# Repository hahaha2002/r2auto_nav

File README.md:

# r2auto_nav
Tánkyu 2310i <br/>
Group 2, Studio 2 <br/>
Ang Kai Jun, David Chong Joon Wei, Ha Zhe Li, Rayner Lim Fang Yuh, Wang Yanxiao Austin <br/>

EG2310 - Fundamentals of Systems Design, AY 21/22, <br/>
Innoovation and Design Programme, National University of Singapore (NUS). <br/>

## Description
The Tánkyu 2310i, developed by NUS IDP students from EG2310, is a modified Robotis Co. Turtlebot 3. It is augmented with LIDAR, NFC-detection, IR-detection and a flywheel firing system to accomplish its set objectives - Autonomous navigation within a closed and connected maze, locating a loading bay demarcated by NFC tags, and firing a ping-pong ball at a target with high IR-signature.

In this repository, we are using Ubuntu 20.04.4, ROS2 Foxy and Python3.6 to explore a closed and connected maze using a left-wall following algorithm.
You may check out our project report under the [Documentations](https://github.com/hahaha2002/r2auto_nav/tree/main/Documentations) folder for more details on our robot and its mission.

## File Organisation
- [Documentations](https://github.com/hahaha2002/r2auto_nav/tree/main/Documentations) folder contain all the documentation of the Tánkyu 2310i, this includes the project report, assembly manual, full software setup guide and end user documentation.
- [navigation.py](https://github.com/hahaha2002/r2auto_nav/blob/main/navigation.py) code contains the main system and wall-following logic. This code also communicates with the mission code to allow the Tánkyu 2310i to engage on the ir signature when the conditions are met.
- [mission.py](https://github.com/hahaha2002/r2auto_nav/blob/main/mission.py) code initiates all the i2c connections and contain the firing algorithm. This code performs all necessary logic processing with the input from the NFC and IR detection systems and communicates the information to the navigation code to allow the Tánkyu 2310i to engage on the ir signature when the conditions are met.
- [Ubuntu_Files](https://github.com/hahaha2002/r2auto_nav/tree/main/Ubuntu_Files) folder is an archive of the miscellaneous code that was tested but not implemented into the final system. The code are functional independently but requires some edits to integrate it into the final system.
- [RPi_Files](https://github.com/hahaha2002/r2auto_nav/tree/main/RPi_Files) folder contains the [factory acceptance test codes](https://github.com/hahaha2002/r2auto_nav/tree/main/RPi_Files/fac_test), all required packages and other test codes for each individual subsystem. 
- [Original_Files](https://github.com/hahaha2002/r2auto_nav/tree/main/Original_Files) folder is an archive of the forked repository from [shihchengyen's r2auto_nav_repository](https://github.com/shihchengyen/r2auto_nav) and is not necessary for the Tankyu 2310i's operations.

## Calibration and configuration
### Navigation Code
Under 'Adjustable variables to calibrate wall follower', you may experiment with different parameters to calibrate the navigation algorithm to suit your needs.
| Variable name| Description| Recommended value  |
| ------------- |:-------------| ---:|
| d | Distance from wall| 0.35 |
| fd| Front distance when approaching a merging wall| d + 0.1|
| reverse_d | Distance to reverse when too close to front wall| 0.20|
| speedchange | Linear speed | 0.17|
| turning_speed_wf_fast| Fast rotate speed, used when avoiding obstacle in front| 0.75|
| turning_speed_wf_slow| Slow rotate speed, used when reversing, finding wall or too close to wall| 0.40|
| snaking_radius | Distance from wall before correcting drift | d - 0.07|
| cornering_speed_constant | Coefficient of speedchange during cornering to prevent over/under steer| 0.5|

### Mission Code
Under 'Adjustable variables to calibrate targeting' you may experiment with different parameters to calibrate the targeting algorithm to suit your needs.
| Variable name| Description| Recommended value  |
| ------------- |:-------------| ---:|
| rotatechange | Angular speed| 0.35 |
| speedchange | Linear speed | 0.20 |
| min_temp_threshold | IR live feed minimum value reference (Appears blue) | 30.0|
| max_temp_threshold | IR live feed maximum value reference (Appears red) | 35.0|
| detecting_threshold | Minimum temperature to identify target as a "Hot target" | 32.0|
| firing_threshold | Acts as a second check after centering target | 35.0|
| ir_offset | Offset angle for each IR sensor orientation (0°→0, 45°→31, 90°→69) | 31.0|

## Operating Instructions

### Installation
Tested on Ubuntu 20.04 - ROS2 Foxy <br/>
For beginners, follow our step-by-step software setup guide in our [documentations](https://github.com/hahaha2002/r2auto_nav/tree/main/Documentations) folder.<br/>
For M1 MacBook users, refer to our [video guide](https://youtu.be/suntoEurFio) for Ubuntu setup and installation. <br/>

1. Install Ubuntu 20.04 and ROS 2 Foxy using the instructions in Section 3.1 of the [Robotis e-manual](https://emanual.robotis.com/docs/en/platform/turtlebot3/quick-start/#pc-setup) (Ensure you click on the "Foxy" tab).
3. Using Ubuntu, complete the RPi in Section 3.2
4. Using Ubuntu, complete the OpenCR setup in Section 3.3 

### Set Up
1. Clone this repository onto your Ubuntu ros2 directory: <br/>
``` 
cd colcon_ws/src/auto_nav
git clone https://github.com/hahaha2002/r2auto_nav.git 
cd colcon_ws
colcon build
```
2. Copy mission.py and the RPi_files folder to the RPi: <br/>
``` 
scp -r <path to r2auto_nav directory>/mission.py ubuntu@<RPi IP address>:~/turtlebot_ws/src 
scp -r <path to r2auto_nav directory>/RPi_files ubuntu@<RPi IP address>:~/turtlebot_ws/src 
```
3. Build the package on RPi: <br/>
``` 
cd turtlebot3_ws 
colcon build 
```
4. Install the pigpio package on RPi and automate the daemon on boot:
```
sudo apt install pigpio
sudo systemctl enable pigpiod
```

### Running Instructions
1. Ssh into the RPi, `ssh ubuntu@<RPi IP Address>`
2. On the RPi, initiate the bring up `ros2 launch turtlebot3_bringup robot.launch.py'
3. On RPi, in the RPi_files directory, Start the targeting code `python3 mission.py`.
4. On Ubuntu, in the r2auto_nav directory, Start the navigation code `python3 navigation.py`.

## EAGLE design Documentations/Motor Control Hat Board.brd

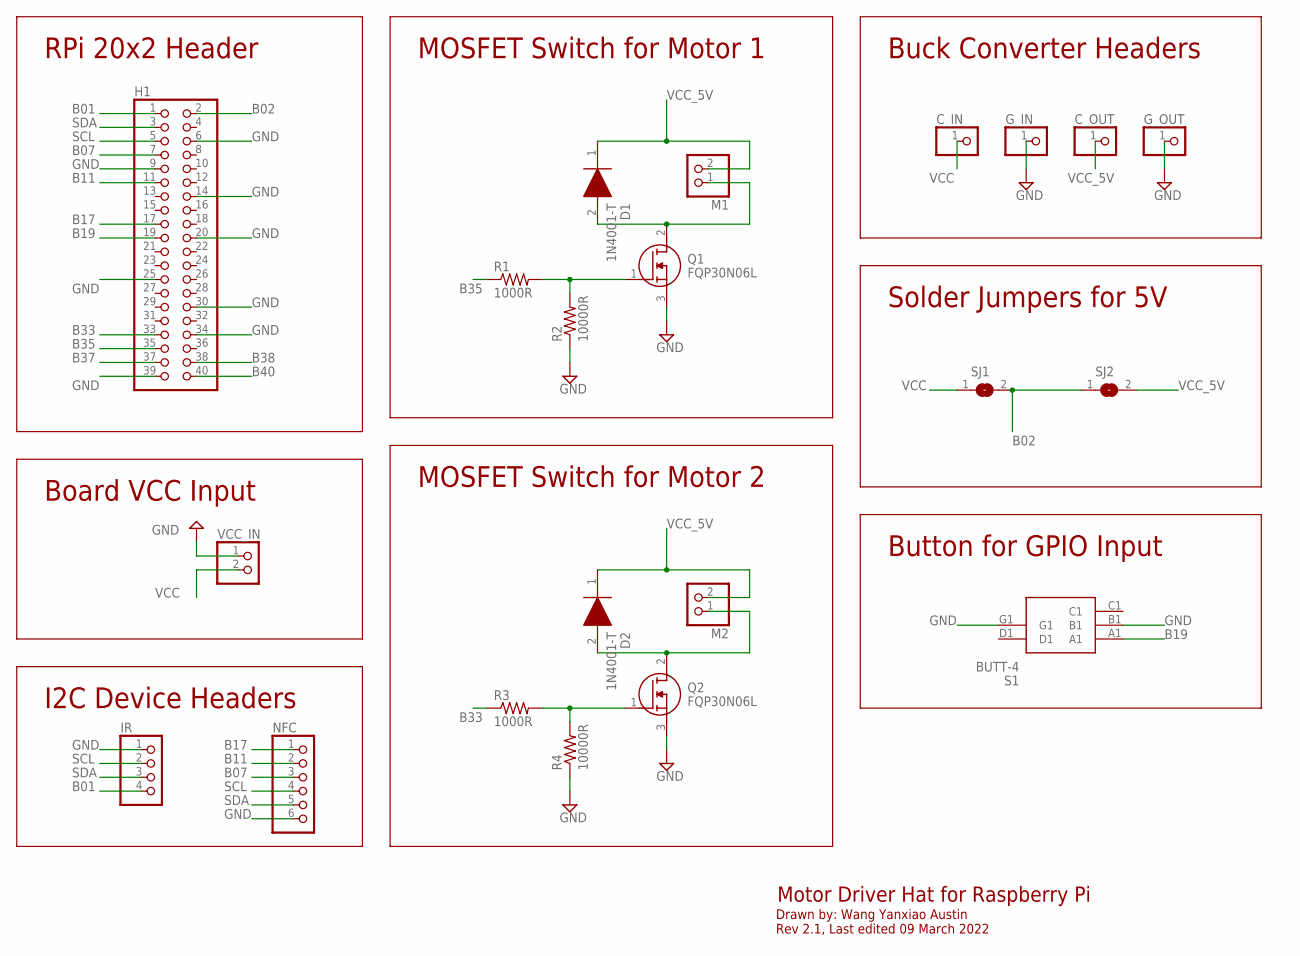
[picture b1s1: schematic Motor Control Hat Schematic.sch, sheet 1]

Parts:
C_IN: PINHD-1X1; 1X01
C_OUT: PINHD-1X1; 1X01
D1, D2: 1N4001-T; DIOAD1408W86L464D236
G_IN: PINHD-1X1; 1X01
G_OUT: PINHD-1X1; 1X01
H1: PINHD-2X20; 2X20
IR: PINHD-1X4; 1X04
M1, M2: PINHD-1X2; 1X02
NFC: PINHD-1X6; 1X06
Q1, Q2: FQP30N06L; TO254P470X1016X2019-3P
R1, R3: 1000R; 0207/10
R2, R4: 10000R; 0207/10
S1: BUTT-4; BUTT4
SJ1, SJ2: SJ
VCC_IN: PINHD-1X2; 1X02

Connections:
B01: H1.1, IR.4
B02: H1.2, SJ1.2, SJ2.1
B07: H1.7, NFC.3
B11: H1.11, NFC.2
B17: H1.17, NFC.1
B19: H1.19, S1.A1
B33: H1.33, R3.1
B35: H1.35, R1.1
B37: H1.37
B38: H1.38
B40: H1.40
GND: G_IN.1, G_OUT.1, H1.6, H1.9, H1.14, H1.20, H1.25, H1.30, H1.34, H1.39, IR.1, NFC.6, Q1.3 (S), Q2.3 (S), R2.1, R4.1, S1.B1, S1.G1, VCC_IN.1
unnamed: Q1.1 (G), R1.2, R2.2
unnamed: D1.2 (A), M1.1, Q1.2 (D)
unnamed: Q2.1 (G), R3.2, R4.2
unnamed: D2.2 (A), M2.1, Q2.2 (D)
SCL: H1.5, IR.2, NFC.4
SDA: H1.3, IR.3, NFC.5
VCC: C_IN.1, SJ1.1, VCC_IN.2
VCC_5V: C_OUT.1, D1.1 (K), D2.1 (K), M1.2, M2.2, SJ2.2

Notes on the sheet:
Motor Driver Hat for Raspberry Pi
Drawn by: Wang Yanxiao Austin Rev 2.1, Last edited 09 March 2022
RPi 20x2 Header
Board VCC Input
MOSFET Switch for Motor 1
MOSFET Switch for Motor 2
I2C Device Headers
Buck Converter Headers
Solder Jumpers for 5V
Button for GPIO Input

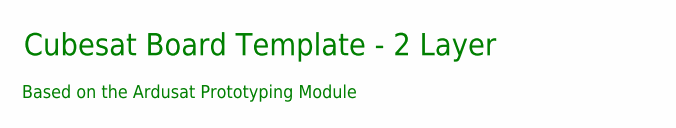
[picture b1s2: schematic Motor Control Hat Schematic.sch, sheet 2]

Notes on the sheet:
Cubesat Board Template - 2 Layer
Based on the Ardusat Prototyping Module

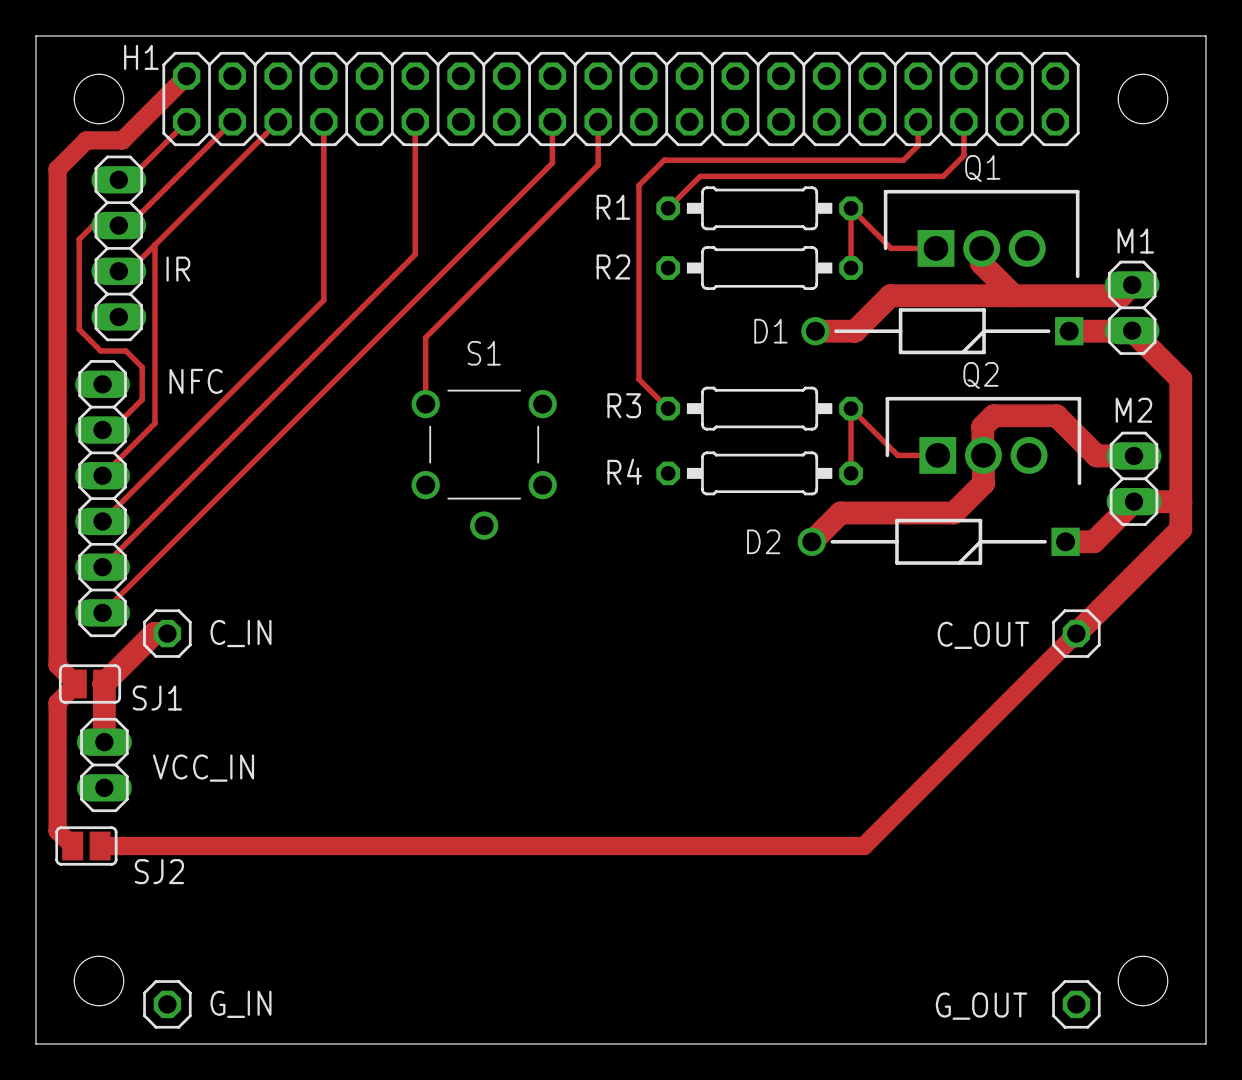
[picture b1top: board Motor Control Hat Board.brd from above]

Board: 2 copper layers, 65.0 x 56.0 mm, 21 parts (0 on the bottom side), 17 nets.

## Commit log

2022-01-19 Added name to users.txt
    Added name as per S1.5 2d
2022-01-19 added Ang Kai Jun and userid
2022-01-19 added username
2022-01-19 testingg
2022-01-19 Updated users.txt with Austin's username
2022-01-19 removed additional stuff
2022-01-19 added rayner username
2022-01-19 removed extra bits
2022-01-19 username
2022-01-25 S3 map
2022-03-17 Added bug 0 algorithm to navigate to specified point
2022-03-17 Added navigation code with improvements
2022-03-18 Moved calibration variables to global variables Added smarter initial move(moves to closest wall) Implemented starting waypoint, if returns without NFC, increases distance from wall
2022-04-02 Added comments
2022-04-02 added bug0 integration, not finalised
2022-04-02 added communication to nav code, not finalised
2022-04-04 bug fixes
2022-04-05 bug fix
2022-04-05 combine bug and navi code
2022-04-05 mission backup from rpi
2022-04-06 added publisher for map2base
2022-04-06 change rotate to increase accuracy
2022-04-07 commented out print statements
2022-04-07 publisher for map2 base for rotate
2022-04-07 ir test
2022-04-07 change motor and servo pin
2022-04-07 switched GPIO pins
2022-04-10 calibration of parameters
2022-04-10 latest version
2022-04-10 made target status publish waypoint temp
2022-04-10 reverted to not publishing waypoint temp, unable to publish int
2022-04-10 reverted to not publishing waypoint temp, cannot publish int
2022-04-11 Added comments and standardised print statements
2022-04-11 rotate test
2022-04-11 changed yaw subscriber
2022-04-11 reverted back to OpenCR yaw data
2022-04-11 looping find target test
2022-04-12 add function to find target while moving forward
2022-04-12 fixed rotate function
2022-04-12 added initial move and adjust parameters
2022-04-12 calibrated firing rotation
2022-04-12 calibrate for final run
2022-04-15 latest code for final maze run
2022-04-16 Updated README with ubuntu installation guide for M1 MacBook
2022-04-18 Organized files
2022-04-18 Commented code for navigation combine
2022-04-18 Added detailed comments
2022-04-20 final code for rpi
2022-04-20 updated GPIO pin
2022-04-20 updated GPIO pins
2022-04-21 orginsed files
2022-04-21 organised files
2022-04-21 added links to external documents
2022-04-21 Added badass image
